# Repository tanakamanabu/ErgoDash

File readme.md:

# About this fork

このリポジトリは [omkbd/ErgoDash](https://github.com/omkbd/ErgoDash) のフォークです。
既存の ErgoDash を改変し、キースイッチのソケット（ホットスワップ）対応版を作ることを目的としています。
オリジナルの ErgoDash については本家リポジトリを参照してください。

This repository is a fork of [omkbd/ErgoDash](https://github.com/omkbd/ErgoDash),
aiming to create a hot-swap socket compatible version of the ErgoDash.
For the original ErgoDash, please refer to the upstream repository.

---

# Notice

2019/5/5にファームウェアをアップデートしました。  
それ以前にハードウェアを作製されていた方はアップデートの必要はありませんが、  
アップデートした方は[ビルドガイドの最終項](https://github.com/omkbd/ErgoDash/blob/master/Doc/build.md#12-firmware%E3%81%AE%E6%9B%B8%E3%81%8D%E8%BE%BC%E3%81%BF)を参照してください。

The firmware has been updated to 5/5/2019.  
If you have previously created hardware, you do not need to update, but if you have updated, please refer to [the last section of the build guide](https://github.com/omkbd/ErgoDash/blob/master/Doc/build-en.md#12-firmware).

# ErgoDash

[Japanese Read me](https://github.com/omkbd/ErgoDash/blob/master/Doc/ergodash_jp.md)

# Layout

# Parts

[ErgoDash PCB](https://github.com/omkbd/ErgoDash/tree/master/PCB)
 × 2  
[ErgoDash Case](https://github.com/omkbd/ErgoDash/tree/master/Case)
 × 2  
Switch (MX-compatible and Alps switches are supported) × 66-70  
Keycap × 66-70  
1N4148 diode × 66-70  
Arduino Pro Micro × 2  
TRRS jack MJ-4PP-9 × 2  
MJTP1117 switch × 2  
TRRS cable × 1  
Micro USB cable × 1  
M2×5mm screw × 22  
M2×8mm screw × 6  
M2×6mm spacer × 14  
Rubber feet × 8

---Option---  
LED WS2812B × 24  
LED 3mm × 66-70  
470Ω resistor × 66-70  
1kΩ resistor × 2  
NchMOSFET IRLML6344TRPbF × 2  

# Firmware

The ErgoDash uses QMK for its firmware, and the code for it is here:
[QMK - ErgoDash directory](https://github.com/qmk/qmk_firmware/tree/master/keyboards/ergodash)
.  

# Build Guide

[Japanese Build Guide](https://github.com/omkbd/ErgoDash/blob/master/Doc/build.md)  
[English Build Guide](https://github.com/omkbd/ErgoDash/blob/master/Doc/build-en.md)

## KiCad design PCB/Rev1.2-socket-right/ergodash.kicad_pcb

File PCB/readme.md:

# ErgoDash PCB

## ソケット（ホットスワップ）対応版

Kailh ソケット対応の作業ディレクトリ（`socket-pcb` ブランチ）:

- `Rev1.2-socket-left/` — **左基板。設計の「正」**。ソケット対応の改変はここで行う
- `Rev1.2-socket-right/` — **右基板。左基板をフリップミラーして生成**したもの（手で直接編集しない）

本家由来の `Rev.1/` `Rev.1.1/` `Rev1.2/` は原則変更しない。詳細な設計方針はリポジトリ直下の `CLAUDE.md` を参照。

### ツールのパス

KiCad 10 同梱のものを使う:

- `kicad-cli` … `C:\Program Files\KiCad\10.0\bin\kicad-cli.exe`
- `python`（pcbnew 用）… `C:\Program Files\KiCad\10.0\bin\python.exe`

### ガーバー出力（推奨：スクリプト）

`PCB/gen_gerbers.ps1` で、各基板の `ergodash.kicad_pcb` からガーバー・ドリル・発注用 zip を
`<基板>/ergodash/` にまとめて再生成する。PowerShell で実行:

```powershell
cd PCB

# 両基板のガーバーを作り直す（各自で基板を編集済みの前提）
.\gen_gerbers.ps1

# 左を編集した後：右をミラー再生成してから両方出力
.\gen_gerbers.ps1 -Mirror

# 片方だけ
.\gen_gerbers.ps1 -Board left
```

発注時は `<基板>/ergodash/ergodash-socket-gerber.zip` をアップロードする。

### ガーバー出力（手動 CLI）

スクリプトを使わない場合は基板ごとに以下。`--board-plot-params` で基板に保存済みの
Plot 設定（出力先 `ergodash/`・レイヤ・Protel 拡張子）をそのまま使うのが要点。

```powershell
$cli = "C:\Program Files\KiCad\10.0\bin\kicad-cli.exe"
$d   = "Rev1.2-socket-left"   # 右なら Rev1.2-socket-right
Remove-Item "$d\ergodash\ergodash-*.g*","$d\ergodash\ergodash-*.drl","$d\ergodash\*.zip" -ErrorAction SilentlyContinue
& $cli pcb export gerbers --board-plot-params -o "$d\ergodash\" "$d\ergodash.kicad_pcb"
& $cli pcb export drill --format excellon --excellon-separate-th -o "$d\ergodash\" "$d\ergodash.kicad_pcb"
```

KiCad GUI なら **File → Plot**（設定は基板に保存済み）→ **Generate Drill Files...**（Excellon / PTH・NPTH 別）でも同じ結果。

### 右基板のミラー再生成

右基板は `mirror_right.py` で左基板をフリップミラー（基板外形の垂直中心軸で `Flip(LEFT_RIGHT)`）して作る。
全要素が B.Cu 側へ移り、ネットは不変（schematic-parity が保たれる）。`gen_gerbers.ps1 -Mirror` が内部でこれを呼ぶが、単体でも:

```powershell
$py = "C:\Program Files\KiCad\10.0\bin\python.exe"
& $py mirror_right.py Rev1.2-socket-right\ergodash.kicad_pcb
```

### 注意点

- **基板を編集したら必ずガーバーを作り直す**（GUI 保存も含む）。古いガーバーのまま発注しないこと。
- **右は左から再生成する**。左を直したら `gen_gerbers.ps1 -Mirror` で右をミラー → 両方出力。右の `.kicad_pcb` を手編集しない。
- **左右の `.kicad_sch` は同一に保つ**（電気設計は左右共通。ミラーはネットを変えない）。
- **KiCad GUI を開いたまま実行しても可**（基板ファイルは読むだけ）。ただし GUI に未保存編集があると古い状態で出力されるので、先に保存する。
- ドリル・Edge_Cuts はヘッダのタイムスタンプで毎回 diff が出るが、形状は不変なので気にしなくてよい。
- **発注前に必ずガーバービューア（KiCad GerbView か発注先のプレビュー）で目視確認**。
- `gen_gerbers.ps1` は日本語コメントを含むため **UTF-8 BOM 付き**で保存すること（Windows PowerShell 5.1 は BOM なしだと文字化けして構文エラーになる）。

## 変更履歴

### [rev.1.1]
・圧電スピーカーを追加（試験的）  
・上記に伴うパーツの配置を調整  
・シルク表記を追加

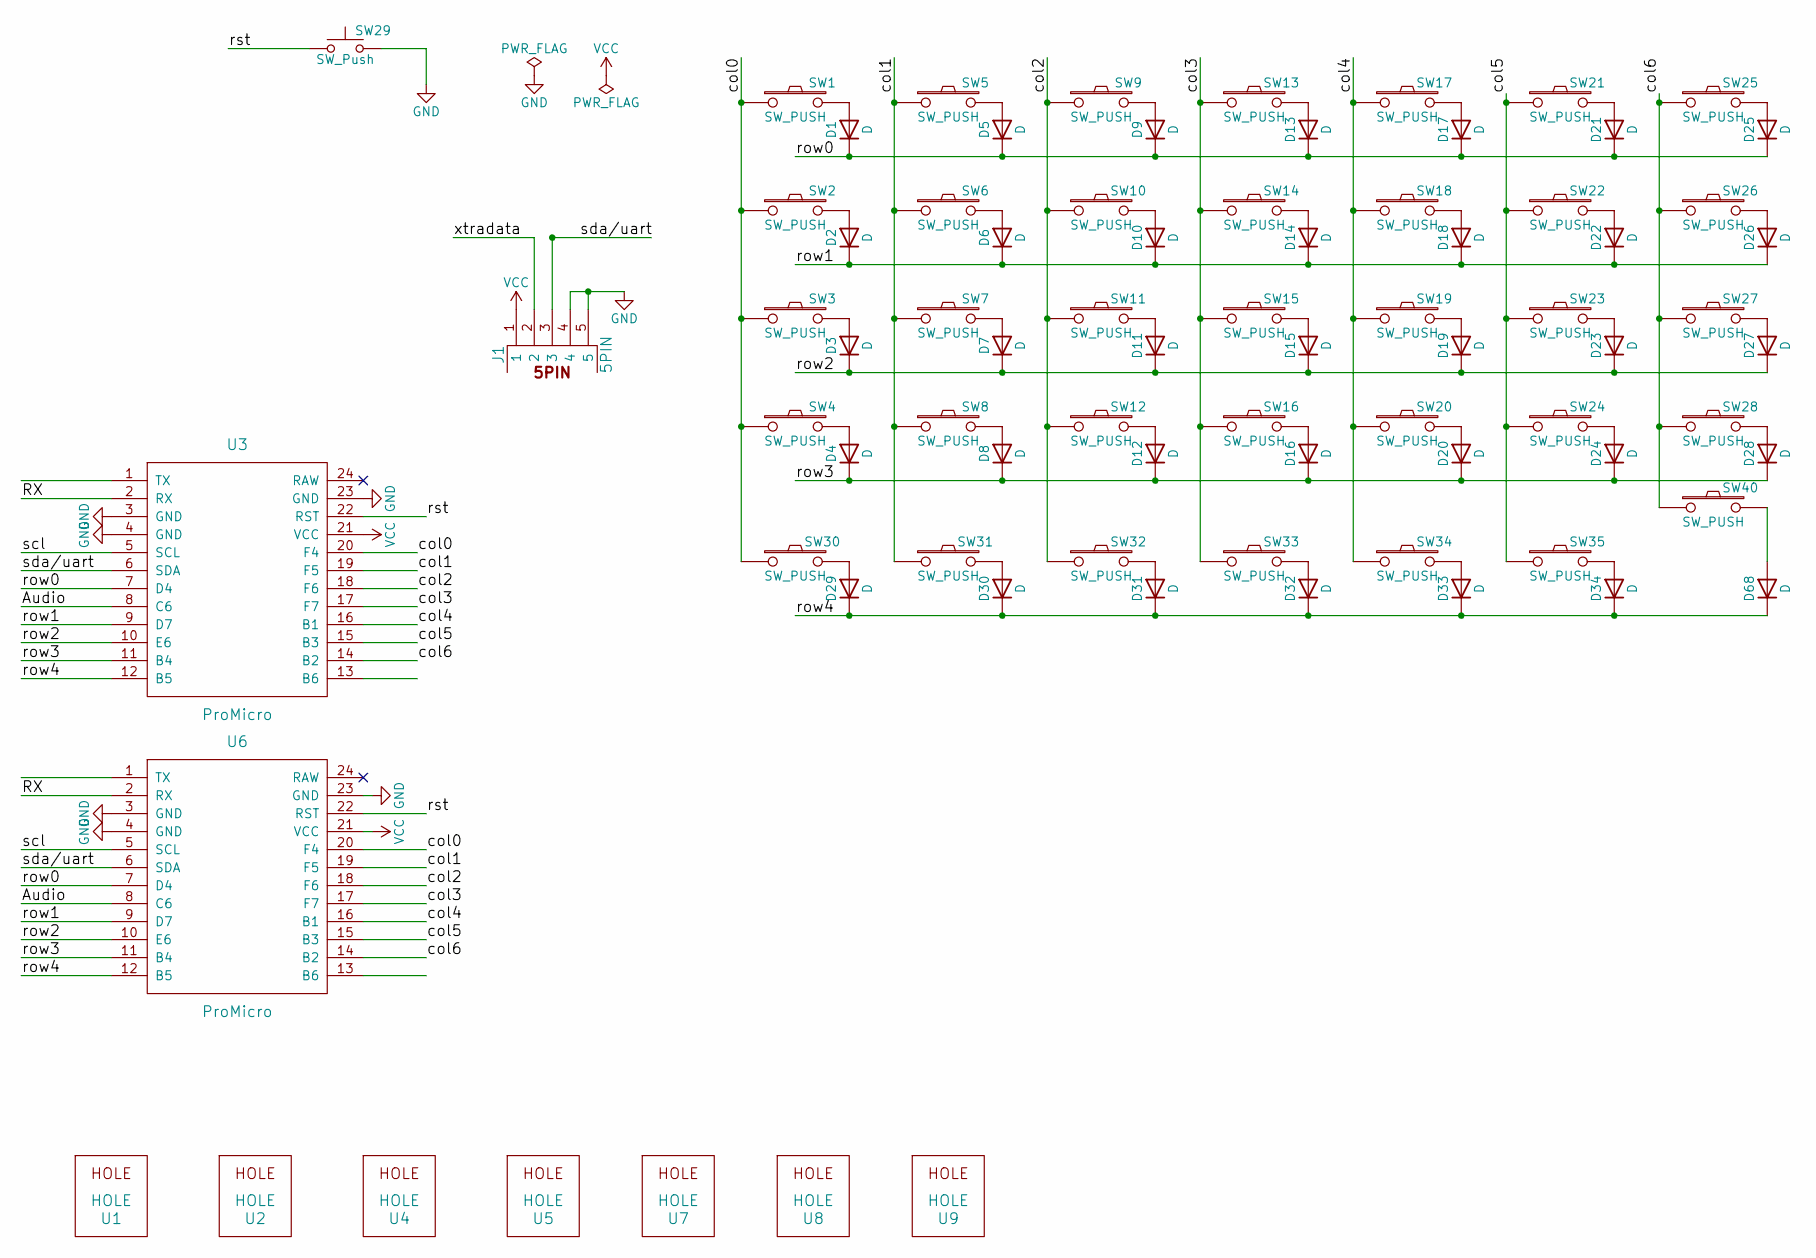
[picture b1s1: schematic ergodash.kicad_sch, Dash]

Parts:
D1, D2, D3, D4, D5, D6, D7, D8, D9, D10, D11, D12, D13, D14, D15, D16, D17, D18, D19, D20, D21, D22, D23, D24, D25, D26, D27, D28, D29, D30, D31, D32, D33, D34: D; Diode_SMD_THT3
D68: D; Diode_SMD_THT2
J1: 5PIN; trrs_jack2
SW1, SW2, SW3, SW4, SW5, SW6, SW7, SW8, SW9, SW10, SW11, SW12, SW13, SW14, SW15, SW16, SW17, SW18, SW19, SW20, SW21, SW22, SW23, SW24, SW25, SW26, SW27, SW28, SW30, SW31, SW32, SW33, SW34, SW35, SW40: SW_PUSH; SW_Hotswap_Kailh_MX_Plated
SW29: SW_Push; tact_switch2
U1, U2, U4, U5, U7, U8, U9: HOLE; hole
U3, U6: ProMicro; ProMicro_rev

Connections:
/Audio: U3.8 (C6), U6.8 (C6)
/RX: U3.2 (RX), U6.2 (RX)
/col0: SW1.1, SW2.1, SW3.1, SW4.1, SW30.1, U3.20 (F4), U6.20 (F4)
/col1: SW5.1, SW6.1, SW7.1, SW8.1, SW31.1, U3.19 (F5), U6.19 (F5)
/col2: SW9.1, SW10.1, SW11.1, SW12.1, SW32.1, U3.18 (F6), U6.18 (F6)
/col3: SW13.1, SW14.1, SW15.1, SW16.1, SW33.1, U3.17 (F7), U6.17 (F7)
/col4: SW17.1, SW18.1, SW19.1, SW20.1, SW34.1, U3.16 (B1), U6.16 (B1)
/col5: SW21.1, SW22.1, SW23.1, SW24.1, SW35.1, U3.15 (B3), U6.15 (B3)
/col6: SW25.1, SW26.1, SW27.1, SW28.1, SW40.1, U3.14 (B2), U6.14 (B2)
/row0: D1.1 (K), D5.1 (K), D9.1 (K), D13.1 (K), D17.1 (K), D21.1 (K), D25.1 (K), U3.7 (D4), U6.7 (D4)
/row1: D2.1 (K), D6.1 (K), D10.1 (K), D14.1 (K), D18.1 (K), D22.1 (K), D26.1 (K), U3.9 (D7), U6.9 (D7)
/row2: D3.1 (K), D7.1 (K), D11.1 (K), D15.1 (K), D19.1 (K), D23.1 (K), D27.1 (K), U3.10 (E6), U6.10 (E6)
/row3: D4.1 (K), D8.1 (K), D12.1 (K), D16.1 (K), D20.1 (K), D24.1 (K), D28.1 (K), U3.11 (B4), U6.11 (B4)
/row4: D29.1 (K), D30.1 (K), D31.1 (K), D32.1 (K), D33.1 (K), D34.1 (K), D68.1 (K), U3.12 (B5), U6.12 (B5)
/rst: SW29.1, U3.22 (RST), U6.22 (RST)
/scl: U3.5 (SCL), U6.5 (SCL)
/sda/uart: J1.3, U3.6 (SDA), U6.6 (SDA)
/xtradata: J1.2
GND: J1.4, J1.5, SW29.2, U3.3 (GND), U3.4 (GND), U3.23 (GND), U6.3 (GND), U6.4 (GND), U6.23 (GND)
unnamed: D1.2 (A), SW1.2
unnamed: D2.2 (A), SW2.2
unnamed: D3.2 (A), SW3.2
unnamed: D4.2 (A), SW4.2
unnamed: D5.2 (A), SW5.2
unnamed: D6.2 (A), SW6.2
unnamed: D7.2 (A), SW7.2
unnamed: D8.2 (A), SW8.2
unnamed: D9.2 (A), SW9.2
unnamed: D10.2 (A), SW10.2
unnamed: D11.2 (A), SW11.2
unnamed: D12.2 (A), SW12.2
unnamed: D13.2 (A), SW13.2
unnamed: D14.2 (A), SW14.2
unnamed: D15.2 (A), SW15.2
unnamed: D16.2 (A), SW16.2
unnamed: D17.2 (A), SW17.2
unnamed: D18.2 (A), SW18.2
unnamed: D19.2 (A), SW19.2
unnamed: D20.2 (A), SW20.2
unnamed: D21.2 (A), SW21.2
unnamed: D22.2 (A), SW22.2
unnamed: D23.2 (A), SW23.2
unnamed: D24.2 (A), SW24.2
unnamed: D25.2 (A), SW25.2
unnamed: D26.2 (A), SW26.2
unnamed: D27.2 (A), SW27.2
unnamed: D28.2 (A), SW28.2
unnamed: D29.2 (A), SW30.2
unnamed: D30.2 (A), SW31.2
unnamed: D31.2 (A), SW32.2
unnamed: D32.2 (A), SW33.2
unnamed: D33.2 (A), SW34.2
unnamed: D34.2 (A), SW35.2
unnamed: D68.2 (A), SW40.2
VCC: J1.1, U3.21 (VCC), U6.21 (VCC)

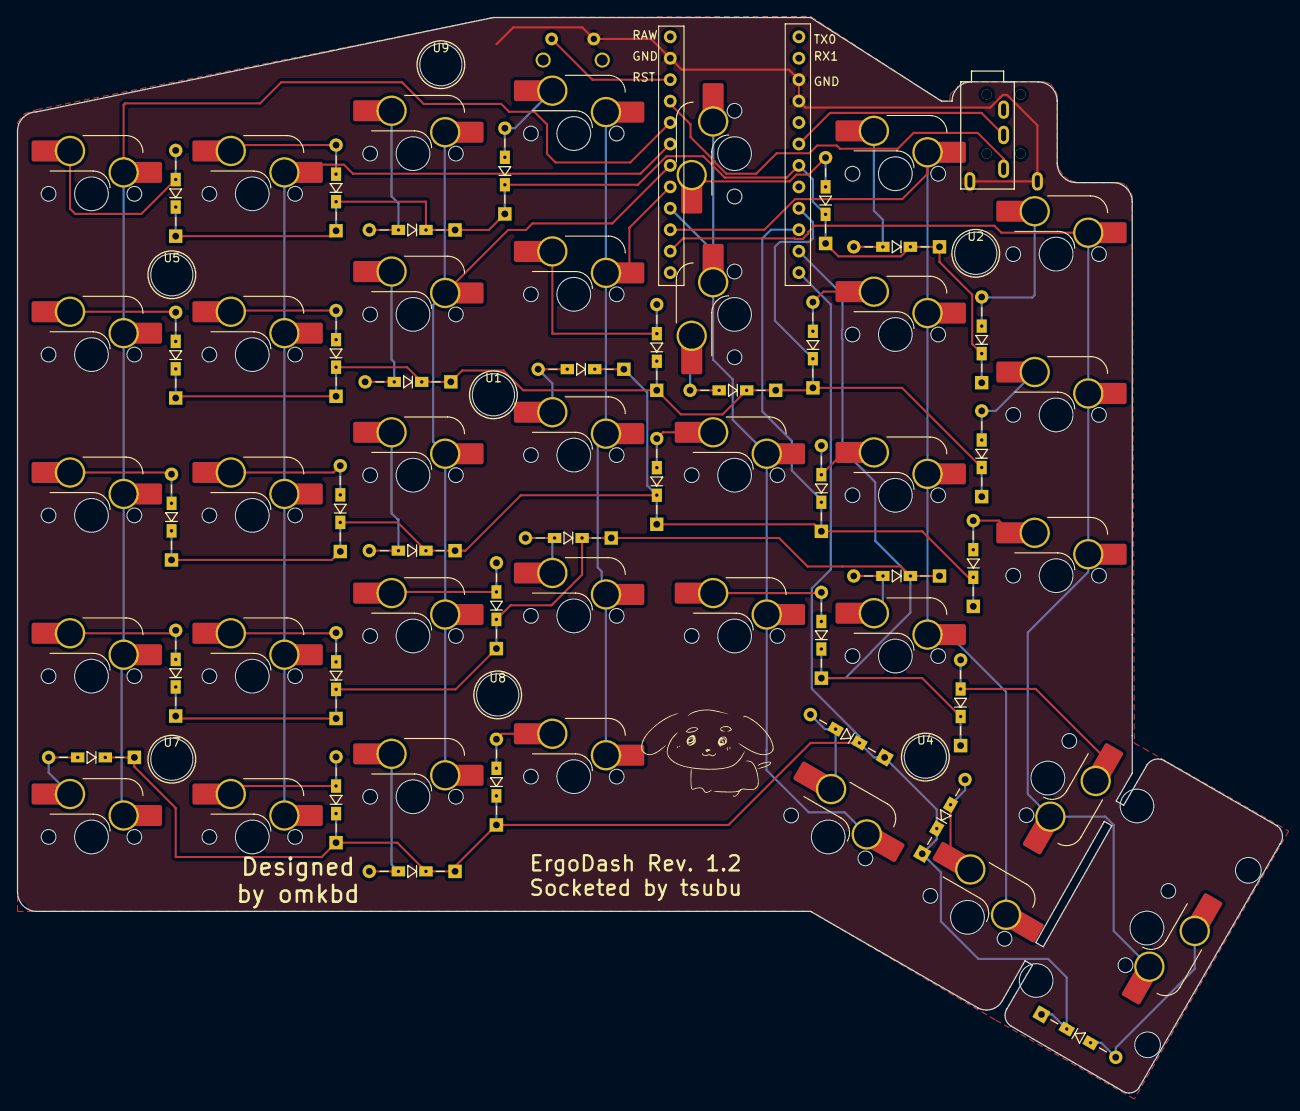
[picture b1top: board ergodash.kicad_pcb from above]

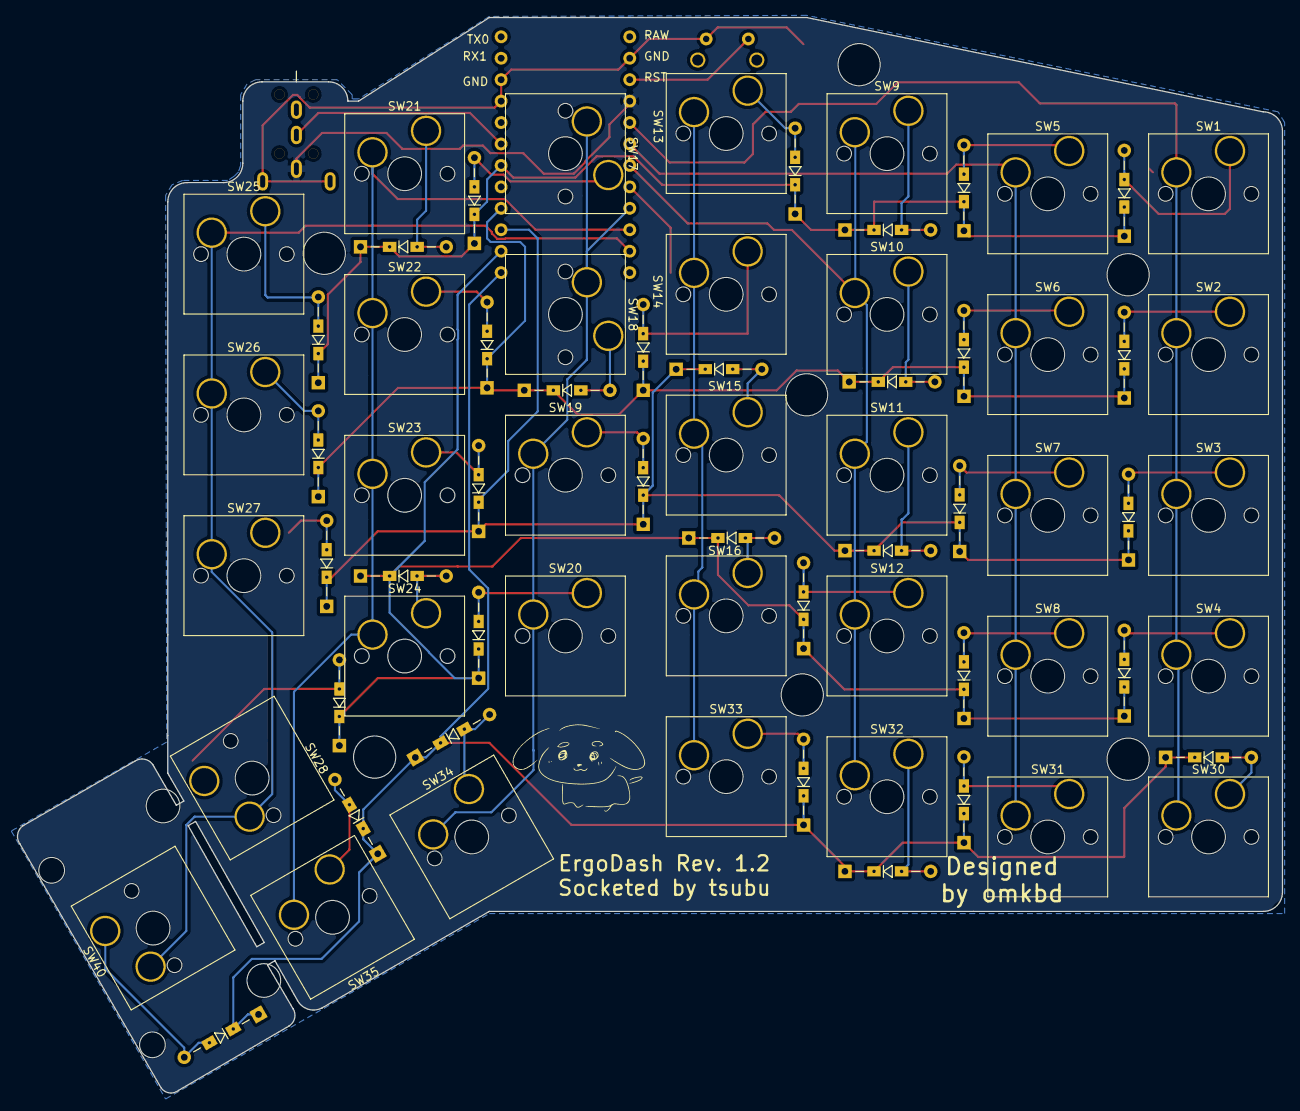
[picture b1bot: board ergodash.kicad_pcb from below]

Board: 2 copper layers, 149.9 x 127.4 mm, 80 parts (36 on the bottom side), 51 nets.
